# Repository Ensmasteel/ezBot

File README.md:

# EzBot Robotics Team Portfolio

Welcome to the EzBot Robotics Team portfolio website! This GitHub Pages site showcases our team's projects, achievements, and innovations in robotics.

## About This Site

This website is built using:
- HTML5
- CSS3
- JavaScript (ES6+)
- GitHub Pages for hosting

## Local Development

To run this site locally:

1. Clone the repository
2. Open `index.html` in your web browser
3. Or serve it using a local server:
   ```bash
   # Using Python 3
   python -m http.server 8000
   
   # Using Node.js (if you have live-server installed)
   npx live-server
   ```

## Deployment

This site is automatically deployed to GitHub Pages when changes are pushed to the main branch.

## Project Structure

```
├── index.html          # Main homepage
├── style.css          # Main stylesheet
├── script.js          # JavaScript functionality
├── README.md          # This file
└── assets/            # Images and other assets (to be added)
```

## Features

- Responsive design that works on all devices
- Smooth scrolling navigation
- Modern CSS with animations
- Clean, professional layout
- Optimized for GitHub Pages

## Customization

To customize this site for your robotics team:

1. Update the team name in `index.html`
2. Modify colors and styling in `style.css`
3. Add your team's projects and member information
4. Include your team's logo and images in an `assets/` folder

## Contributing

Team members can contribute by:
1. Forking the repository
2. Making changes
3. Submitting a pull request

## Contact

For questions about this website, please contact the EzBot team.

---

Built with ❤️ by the EzBot Robotics Team

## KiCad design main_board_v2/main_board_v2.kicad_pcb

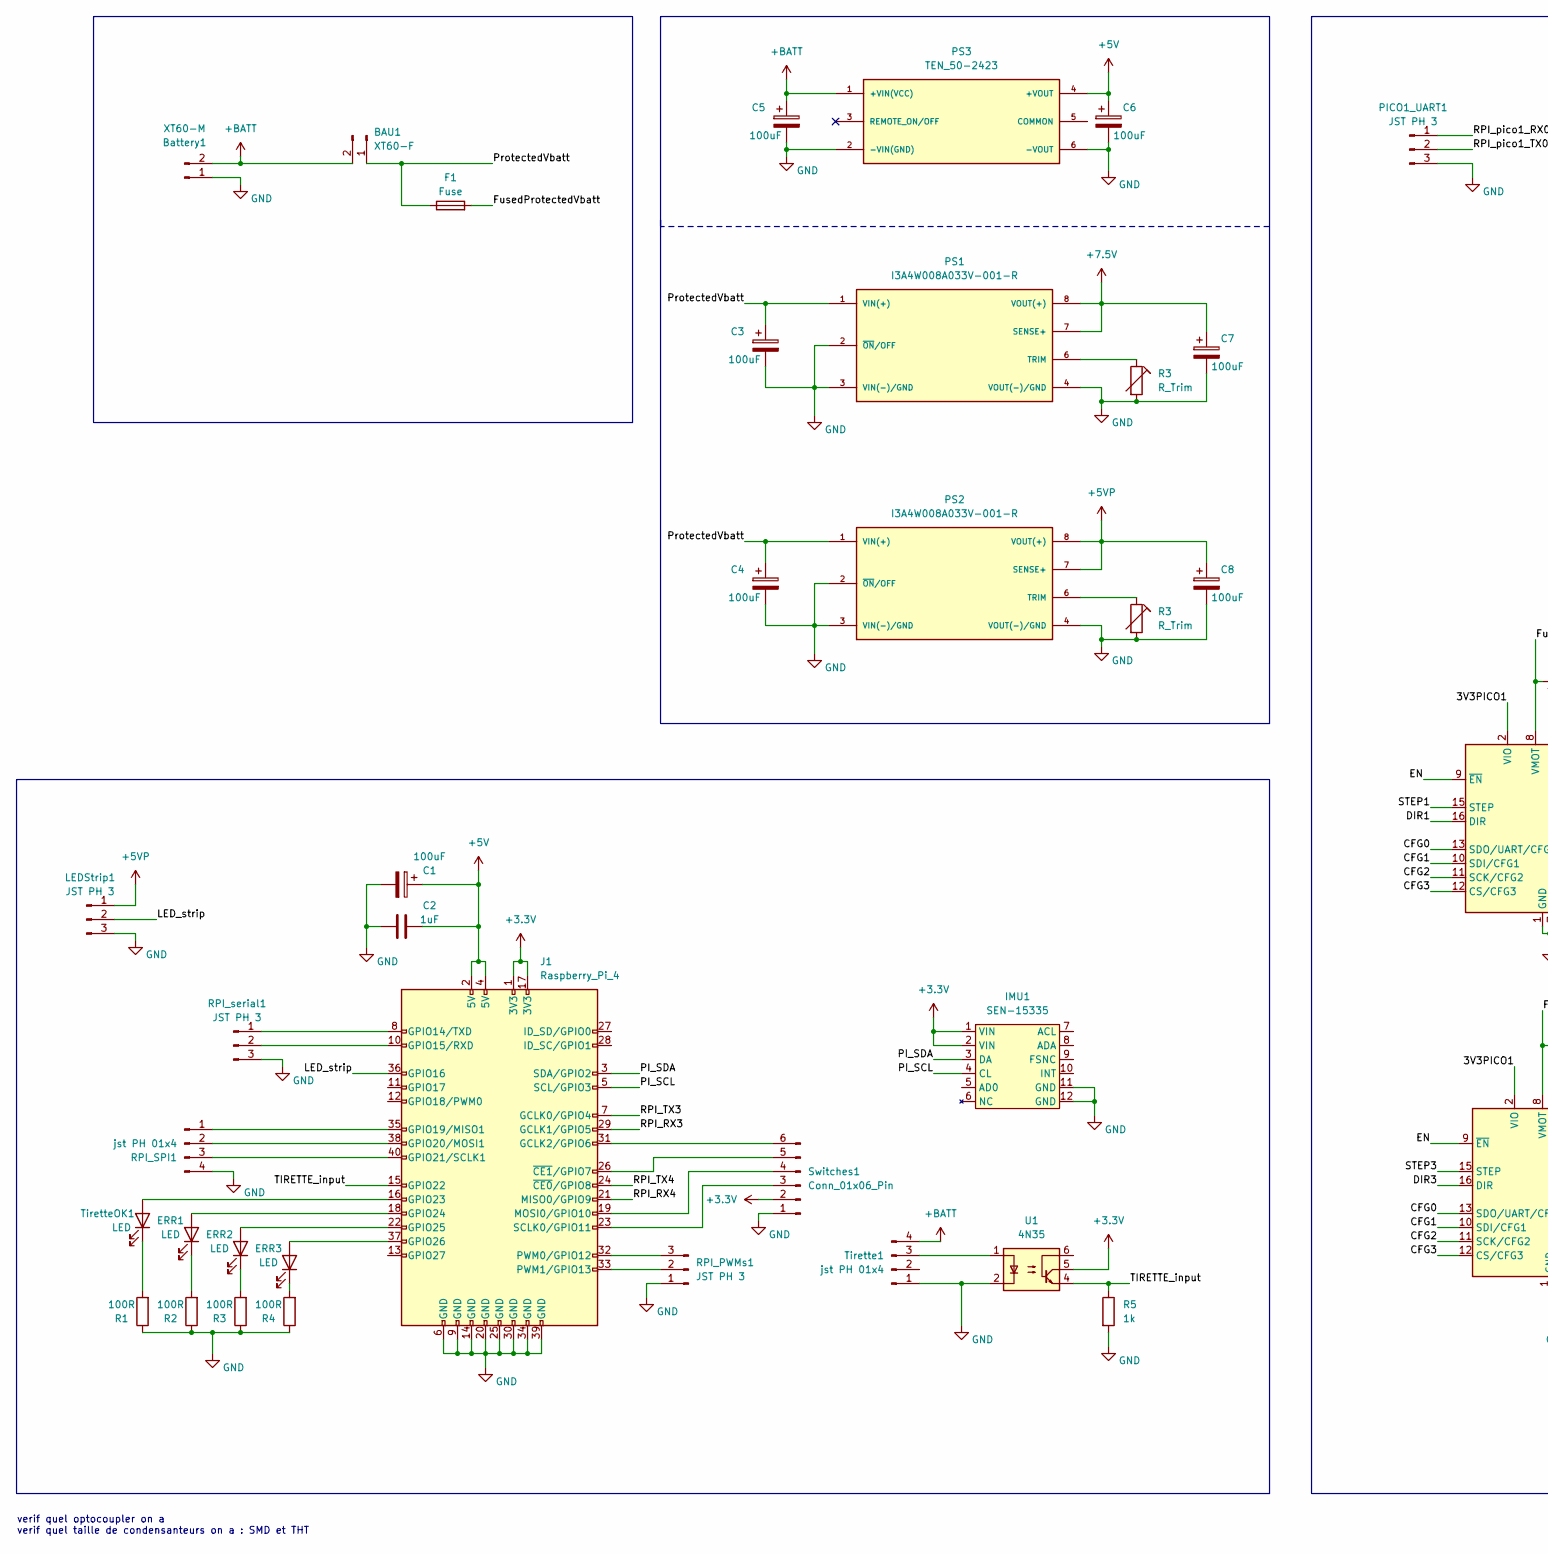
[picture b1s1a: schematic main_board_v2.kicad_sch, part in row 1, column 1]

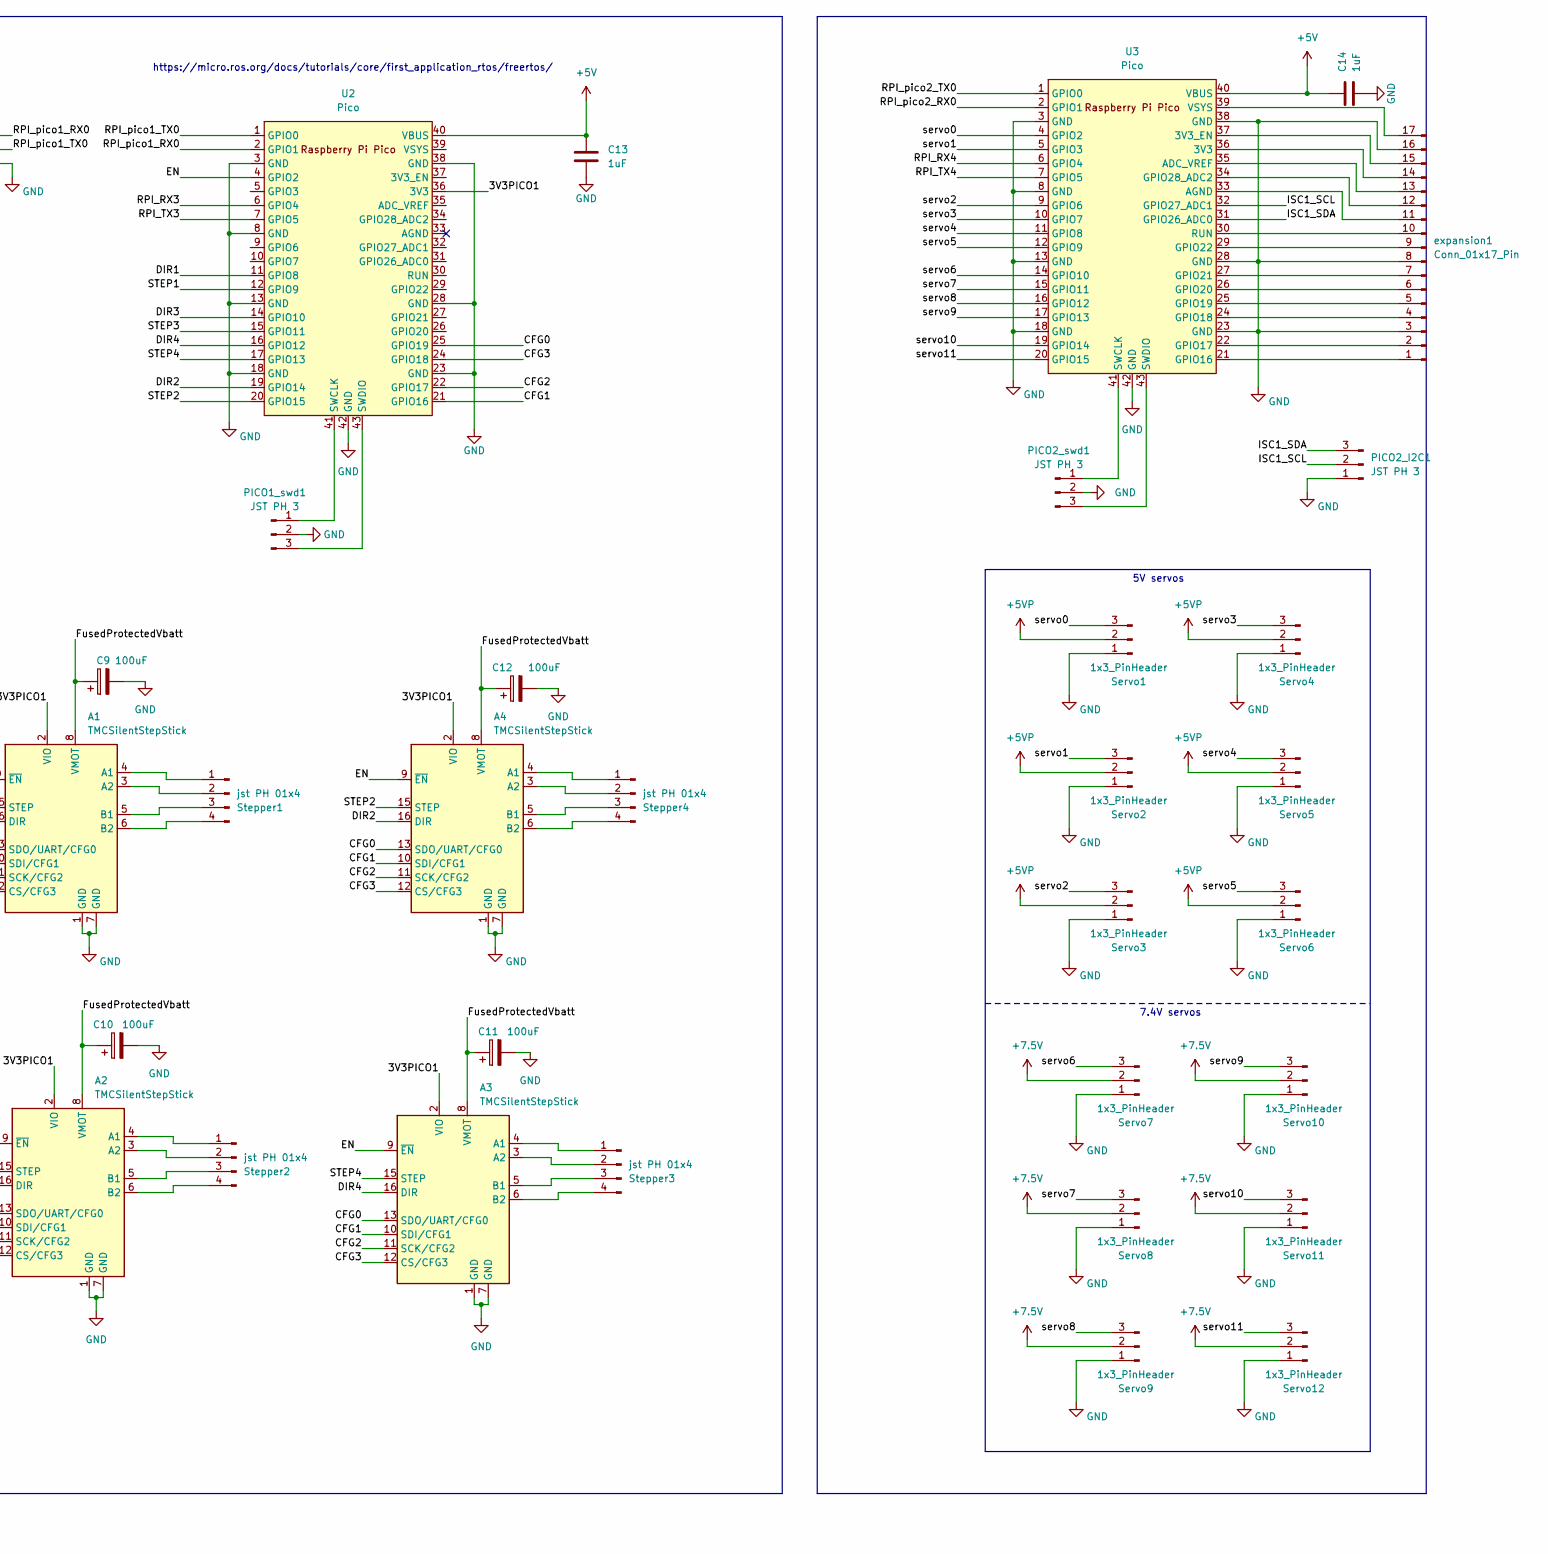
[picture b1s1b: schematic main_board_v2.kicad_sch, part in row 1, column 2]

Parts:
A1, A2, A3, A4: TMCSilentStepStick; TMCStick
BAU1: XT60-F; AMASS_XT60-F_1x02_P7.20mm_Vertical
Battery1: XT60-M; AMASS_XT60-M_1x02_P7.20mm_Vertical
C1, C3, C4, C5, C6, C7, C8, C9, C10, C11, C12: 100uF; C_Radial_D6.3mm_H11.0mm_P2.50mm
C2, C13, C14: 1uF; C_0805_2012Metric
ERR1, ERR2, ERR3: LED; LED_0805_2012Metric
F1: Fuse; Fuseholder_Blade_ATO_Littelfuse_Pudenz_2_Pin
IMU1: SEN-15335
J1: Raspberry_Pi_4
LEDStrip1: JST PH 3; JST_PH_B3B-PH-K_1x03_P2.00mm_Vertical
PICO1_UART1, PICO1_swd1, PICO2_I2C1, PICO2_swd1: JST PH 3; JST_PH_B3B-PH-K_1x03_P2.00mm_Vertical
PS1, PS2: I3A4W008A033V-001-R; CONV_I3A4W008A033V-001-R
PS3: TEN_50-2423; CONV_TEN_30-2423
R1, R2, R3, R4: 100R; R_1206_3216Metric
R5: 1k; R_1206_3216Metric
RPI_PWMs1: JST PH 3; JST_PH_B3B-PH-K_1x03_P2.00mm_Vertical
RPI_SPI1: jst PH 01x4; JST_PH_B4B-PH-K_1x04_P2.00mm_Vertical
RPI_serial1: JST PH 3; JST_PH_B3B-PH-K_1x03_P2.00mm_Vertical
Servo1, Servo2, Servo3, Servo4, Servo5, Servo6, Servo7, Servo8, Servo9, Servo10, Servo11, Servo12: 1x3_PinHeader; PinHeader_1x03_P2.54mm_Vertical
Stepper1, Stepper2, Stepper3, Stepper4: jst PH 01x4; JST_PH_B4B-PH-K_1x04_P2.00mm_Vertical
Switches1: Conn_01x06_Pin; JST_PH_B6B-PH-K_1x06_P2.00mm_Vertical
Tirette1: jst PH 01x4; JST_PH_B4B-PH-K_1x04_P2.00mm_Vertical
TiretteOK1: LED; LED_0805_2012Metric
U1: 4N35; DIP-6_W7.62mm
U2, U3: Pico; RPi_Pico_SMD_TH
expansion1: Conn_01x17_Pin; PinHeader_1x17_P2.54mm_Vertical

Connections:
+3.3V: IMU1.1 (VIN), IMU1.2 (VIN), J1.1 (3V3), J1.17 (3V3), Switches1.2, U1.5
+5V: C1.1, C2.2, C6.1, C13.1, C14.1, J1.2 (5V), J1.4 (5V), PS3.4 (+VOUT), U2.40 (VBUS), U3.40 (VBUS)
+5VP: C8.1, LEDStrip1.1, PS2.7 (SENSE+), PS2.8 (VOUT(+)), Servo1.2, Servo2.2, Servo3.2, Servo4.2, Servo5.2, Servo6.2
+7.5V: C7.1, PS1.7 (SENSE+), PS1.8 (VOUT(+)), Servo7.2, Servo8.2, Servo9.2, Servo10.2, Servo11.2, Servo12.2
+BATT: BAU1.2, Battery1.2, C5.1, PS3.1 (+VIN(VCC)), Tirette1.4
/3V3PICO1: A1.2 (VIO), A2.2 (VIO), A3.2 (VIO), A4.2 (VIO), U2.36 (3V3)
/CFG0: A1.13 (SDO/UART/CFG0), A2.13 (SDO/UART/CFG0), A3.13 (SDO/UART/CFG0), A4.13 (SDO/UART/CFG0), U2.25 (GPIO19)
/CFG1: A1.10 (SDI/CFG1), A2.10 (SDI/CFG1), A3.10 (SDI/CFG1), A4.10 (SDI/CFG1), U2.21 (GPIO16)
/CFG2: A1.11 (SCK/CFG2), A2.11 (SCK/CFG2), A3.11 (SCK/CFG2), A4.11 (SCK/CFG2), U2.22 (GPIO17)
/CFG3: A1.12 (CS/CFG3), A2.12 (CS/CFG3), A3.12 (CS/CFG3), A4.12 (CS/CFG3), U2.24 (GPIO18)
/DIR1: A1.16 (DIR), U2.11 (GPIO8)
/DIR2: A4.16 (DIR), U2.19 (GPIO14)
/DIR3: A2.16 (DIR), U2.14 (GPIO10)
/DIR4: A3.16 (DIR), U2.16 (GPIO12)
/EN: A1.9 (~EN), A2.9 (~EN), A3.9 (~EN), A4.9 (~EN), U2.4 (GPIO2)
/FusedProtectedVbatt: A1.8 (VMOT), A2.8 (VMOT), A3.8 (VMOT), A4.8 (VMOT), C9.1, C10.1, C11.1, C12.1, F1.2
/ISC1_SCL: PICO2_I2C1.2, U3.32 (GPIO27_ADC1)
/ISC1_SDA: PICO2_I2C1.3, U3.31 (GPIO26_ADC0)
/LED_strip: J1.36 (GPIO16), LEDStrip1.2
/PI_SCL: IMU1.4 (CL), J1.5 (SCL/GPIO3)
/PI_SDA: IMU1.3 (DA), J1.3 (SDA/GPIO2)
/ProtectedVbatt: BAU1.1, C3.1, C4.1, F1.1, PS1.1 (VIN(+)), PS2.1 (VIN(+))
/RPI_RX3: J1.29 (GCLK1/GPIO5), U2.6 (GPIO4)
/RPI_RX4: J1.21 (MISO0/GPIO9), U3.6 (GPIO4)
/RPI_TX3: J1.7 (GCLK0/GPIO4), U2.7 (GPIO5)
/RPI_TX4: J1.24 (~CE0/GPIO8), U3.7 (GPIO5)
/RPI_pico1_RX0: PICO1_UART1.1, U2.2 (GPIO1)
/RPI_pico1_TX0: PICO1_UART1.2, U2.1 (GPIO0)
/RPI_pico2_RX0: U3.2 (GPIO1)
/RPI_pico2_TX0: U3.1 (GPIO0)
/STEP1: A1.15 (STEP), U2.12 (GPIO9)
/STEP2: A4.15 (STEP), U2.20 (GPIO15)
/STEP3: A2.15 (STEP), U2.15 (GPIO11)
/STEP4: A3.15 (STEP), U2.17 (GPIO13)
/TIRETTE_input: J1.15 (GPIO22), R5.1, U1.4
/servo0: Servo1.3, U3.4 (GPIO2)
/servo1: Servo2.3, U3.5 (GPIO3)
/servo2: Servo3.3, U3.9 (GPIO6)
/servo3: Servo4.3, U3.10 (GPIO7)
/servo4: Servo5.3, U3.11 (GPIO8)
/servo5: Servo6.3, U3.12 (GPIO9)
/servo6: Servo7.3, U3.14 (GPIO10)
/servo7: Servo8.3, U3.15 (GPIO11)
/servo8: Servo9.3, U3.16 (GPIO12)
/servo9: Servo10.3, U3.17 (GPIO13)
/servo10: Servo11.3, U3.19 (GPIO14)
/servo11: Servo12.3, U3.20 (GPIO15)
unnamed: A1.4 (A1), Stepper1.1
unnamed: A1.3 (A2), Stepper1.2
unnamed: A1.5 (B1), Stepper1.3
unnamed: A1.6 (B2), Stepper1.4
unnamed: A2.4 (A1), Stepper2.1
unnamed: A2.3 (A2), Stepper2.2
unnamed: A2.5 (B1), Stepper2.3
unnamed: A2.6 (B2), Stepper2.4
unnamed: A3.4 (A1), Stepper3.1
unnamed: A3.3 (A2), Stepper3.2
unnamed: A3.5 (B1), Stepper3.3
unnamed: A3.6 (B2), Stepper3.4
unnamed: A4.4 (A1), Stepper4.1
unnamed: A4.3 (A2), Stepper4.2
unnamed: A4.5 (B1), Stepper4.3
unnamed: A4.6 (B2), Stepper4.4
unnamed: ERR1.2 (A), J1.18 (GPIO24)
unnamed: ERR1.1 (K), R2.2
unnamed: ERR2.2 (A), J1.22 (GPIO25)
unnamed: ERR3.2 (A), J1.37 (GPIO26)
unnamed: ERR3.1 (K), R4.2
unnamed: J1.31 (GCLK2/GPIO6), Switches1.6
unnamed: J1.8 (GPIO14/TXD), RPI_serial1.1
unnamed: J1.10 (GPIO15/RXD), RPI_serial1.2
unnamed: J1.35 (GPIO19/MISO1), RPI_SPI1.1
unnamed: J1.38 (GPIO20/MOSI1), RPI_SPI1.2
unnamed: J1.40 (GPIO21/SCLK1), RPI_SPI1.3
unnamed: J1.16 (GPIO23), TiretteOK1.2 (A)
unnamed: J1.19 (MOSI0/GPIO10), Switches1.4
unnamed: J1.32 (PWM0/GPIO12), RPI_PWMs1.3
unnamed: J1.33 (PWM1/GPIO13), RPI_PWMs1.2
unnamed: J1.23 (SCLK0/GPIO11), Switches1.3
unnamed: J1.26 (~CE1/GPIO7), Switches1.5
unnamed: PICO1_swd1.1, U2.41 (SWCLK)
unnamed: PICO1_swd1.3, U2.43 (SWDIO)
unnamed: PICO2_swd1.1, U3.41 (SWCLK)
unnamed: PICO2_swd1.3, U3.43 (SWDIO)
unnamed: Tirette1.3, U1.1
unnamed: R1.2, TiretteOK1.1 (K)
unnamed: U3.36 (3V3), expansion1.14
unnamed: U3.37 (3V3_EN), expansion1.15
unnamed: U3.35 (ADC_VREF), expansion1.13
unnamed: U3.33 (AGND), expansion1.11
unnamed: U3.21 (GPIO16), expansion1.1
unnamed: U3.22 (GPIO17), expansion1.2
unnamed: U3.24 (GPIO18), expansion1.4
unnamed: U3.25 (GPIO19), expansion1.5
unnamed: U3.26 (GPIO20), expansion1.6
unnamed: U3.27 (GPIO21), expansion1.7
unnamed: U3.29 (GPIO22), expansion1.9
unnamed: U3.34 (GPIO28_ADC2), expansion1.12
unnamed: U3.30 (RUN), expansion1.10
unnamed: U3.39 (VSYS), expansion1.17

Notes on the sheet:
5V servos
verif quel optocoupler on a verif quel taille de condensanteurs on a : SMD et THT
https://micro.ros.org/docs/tutorials/core/first_application_rtos/freertos/
7.4V servos

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
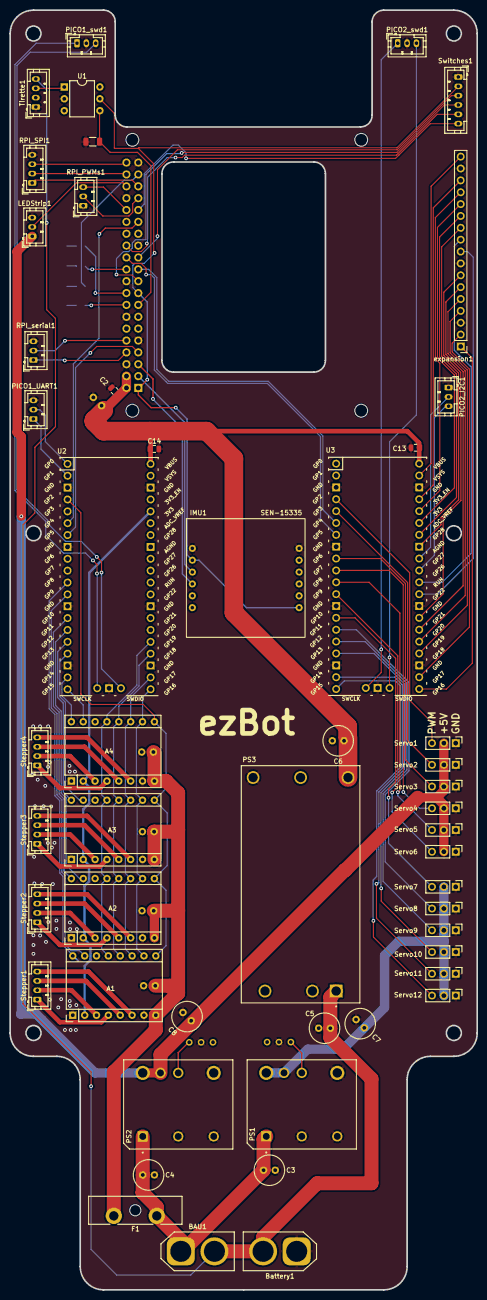
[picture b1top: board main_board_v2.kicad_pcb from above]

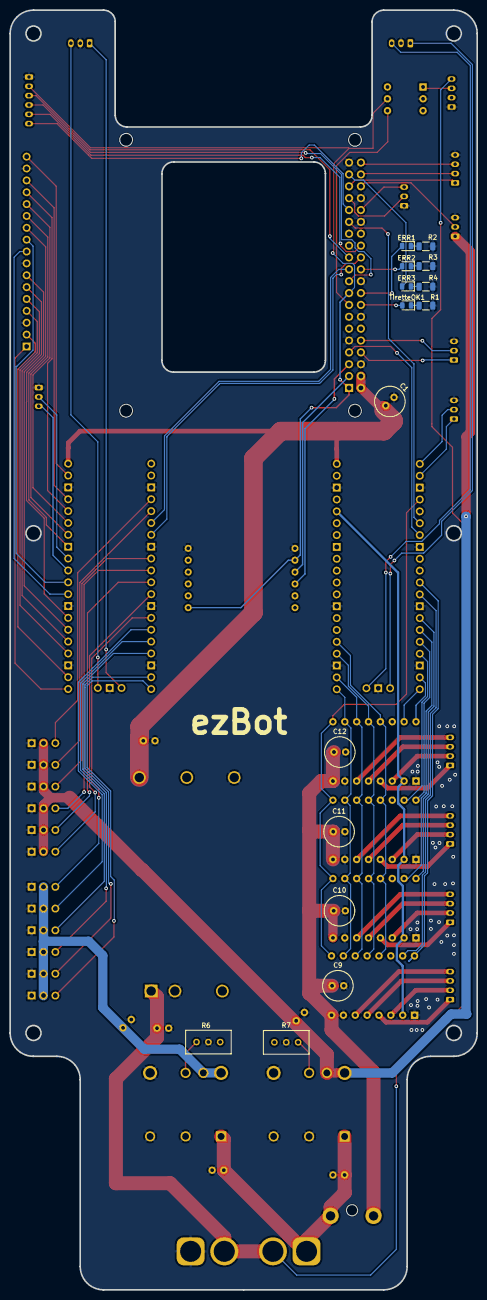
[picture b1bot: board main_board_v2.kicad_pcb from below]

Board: 2 copper layers, 100.0 x 274.0 mm, 67 parts (15 on the bottom side), 102 nets.

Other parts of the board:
R6, R7: R_Trim; Potentiometer_Bourns_3296W_Vertical

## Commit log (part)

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2023-08-03 Creation of new orphan branch "electronic"
2023-08-04 Test
2023-08-04 Added Humble Hawksbill Image for readme
2023-08-04 Modified README.md
2023-08-04 Created ROS2 workspace with colcon
2023-08-05 Added main files
    Currently only one main-skeleton, but sub skeletons can be used for sub assemblies
2023-08-05 Added Fasteners and others
2023-08-06 Amost Finished Holonimc wheel
    Missing holes and (3D printed) Hub
2023-08-06 These nuts are M3
2023-08-08 Added Nema17 motor
2023-08-08 Almost finished holonomic wheel
2023-09-11 Added rules and rules images
    Images could be used in some readmes
2023-09-11 Added table to main readme
2023-09-11 changed path README.md
2023-09-12 Added png version of main vinyl
2023-09-12 Added stl of corrected fixed table
2023-09-12 Added texture file and textured the table in Blender
2023-10-17 Nema23
2023-10-17 Created project
2023-10-17 No, this is the project's creation
2023-10-23 Created MotorAndWheelAssembly and added many things to skeleton
2023-10-25 Center base and center chassis creation
2023-10-26 Added the four rails
2023-10-26 Changed the propulsion block chassis
    now kind of works
    still needs mounting holes
2023-10-28 Added bolts to propulsion module and parameter for width
2023-10-28 Changed some constraints
2023-10-28 Before scenes schenanigans
2023-10-28 Tested parameter unitsize -> works kinda
2023-10-30 Reduced joint thickness so that NEMA17 motor can be inserted
2023-11-01 Passage cables moteurs chassis centre et chassis propulsion
2023-11-01 inserts in center chassis
2023-11-01 Added chanfers
2023-11-01 Started top
2023-11-02 Ajout de vis pour rail NE
2023-11-02 Holes ans screws
2023-11-02 All rails have now bottom holes
2023-11-03 Added PCB placeholder
2023-11-03 Modified TopCenterChassis
2023-11-03 Hid TopSkeleton
2023-11-03 Added Holes to Rails
2023-11-03 Mine is better
2023-11-04 Added some homemade footprints
    TMCSilentStepStick and IMU
2023-11-04 Added battery placeholder
2023-11-04 Used parameter for M3 holes on TopCenterChassis
2023-11-04 Battery Work
2023-11-04 Added battery prototype to main product
2023-11-05 Added traco and tdk regulators, and IMU and more
2023-11-05 Added headers and corrected 3d model of pico
2023-11-13 Work, lots of
2023-11-23 Work it seams
2023-11-23 Added plug for raspberry switches and corrected all DRCs
2023-11-24 Created part from product to export to gazebo
2023-11-24 Added .dae file of the table with UV map
2023-11-24 removed unnecessaty built files and added ezbot_gazebo pkg
2023-11-29 Added ldrobot lidar and some launch files
2023-11-29 Removed empty folder
2023-11-29 Added .gitignore file with the log, build, and install folders
2023-12-01 Lidar transition launch file now works
2023-12-01 Added testing folder for RP pico (propulsion)
2023-12-18 Robot description and simulation
2023-12-18 Rm folder
2023-12-18 Added robot description, launch file for simul (based on Mathys myBot)
2023-12-18 updated scale
2023-12-18 Added verbose launch of simulation
2023-12-18 Changed color of one of the wheels
2023-12-18 Added workflow in ezBot branch
2023-12-18 removed tabs
2023-12-19 Attempt to fix copyright issue
2023-12-19 removed empty file
2023-12-22 joystick and launch file
2023-12-22 robot description changes
2023-12-22 Delete .vscode directory
    do not push .vscode directory
2023-12-22 Added omnidirectional controller from axebot
2024-01-10 Changed dimensions of lidar and camera resolution.
2024-01-11 Added world folder to the install path the launch file for the simulation can now be launched from anywhere
2024-01-12 Changed lidar frame name
2024-01-12 Fixed the bug where we could only launch from src
    We could only launch launch_sim.launch.py from /src directory as the path were relative
2024-01-12 added an aruco marker on top of the robot
2024-01-12 work
2024-01-17 tag aruco on the robot
2024-01-17 Changed mu1
2024-01-17 Added min_depth tag to (almost) eliminate the robot from drifting
2024-01-17 Added real robot launch file
2024-01-17 Added main rpi-pico project It is for now a platformio progect and based on articulated's robotic project
2024-01-17 Made a hardware interface based on diffdrive-arduino ! Not tested yet !
2024-01-19 Added homemade controller to not user ros2control
2024-01-24 Added docker files for arm, and scripts for build and run
2024-01-24 Homemade controller
    Now sends correctly to emulated serial, needs testing with real serial
2024-01-24 Controller configuration for ros2_control
    Not in use currentyl
2024-01-24 launch file for the real robot
2024-01-24 added marker detection for the second camera
2024-01-24 Updated RailDrillingTool and LidarBase
2024-01-24 Changed _ to .
2024-01-26 Changed from Opencv to opencv-python in dependencies
2024-01-26 changed again to python 3
2024-01-29 Added solar panel model
2024-01-29 Added solar panel to table
2024-01-29 changed image name and added display
2024-01-29 Added comment test
2024-01-29 removed temp package.xml
2024-01-29 Added it back
2024-01-29 WILL THE RUN WORK ??
2024-01-29 Changed gazebo omni drive kinematics now drive straight chen cmd_vel = x
2024-01-31 removed unused omnidirectional controller
2024-02-05 Changed from 21700 to 18650
    Still need to change names of parts and instances
2024-03-30 Changed robot height to actual height (343mm rails)
2024-03-30 Fixed the PCB's position
    the PCB'ss positition was deriver from the placeholder's position. Howerver, the PCB placeholder was not dimensioned correctly (dimmensioned using robot's contraints and not pure dimensions)
2024-03-31 Added holes to rails for PCB (only center for now)
2024-03-31 Added assembly of rail drilling tool and one rail and fixed tool
    The product is used to verify the alignment of the holes in the tool and in the rails (SW for now)
2024-03-31 Print file of the rail drilling tool
2024-04-04 I don't know why every file changed but made slots to the top center
2024-04-09 Rework on the battery and the top chassis
2024-04-09 Added Lidar spacer, and support
    also modified the existing "lidar base" part to fit the new battery
2024-04-10 Printed this version of the Lidar Base and Spacer
2024-04-17 Printed test receiver plate and added wheel hubs
2024-04-18 Added a way to fix the receiver plate
2024-04-21 Set logger to info in launch file if not set
2024-04-21 Be able to launch docker on raspberry's boot (not used)
2024-04-21 removed ldlidar submodule
2024-04-21 Renamed ezbot_gazebo to ezbot_simulation
2024-04-21 Moved launch_sim.launch.py to simulation folder
2024-04-21 rm unnecessary turtle launch file
2024-04-21 Renamed ezbot_descr_simul to ezbot_robot
    This is to make a clearer sepperation between simulation and real robot codebases
2024-04-21 Changed all instances of ezbot_descr_simul to ezbot_robot
2024-04-22 ros2_control seem to be working, testing the communication with Pico
2024-04-22 Changed serial port and how yaml file is configured
2024-04-23 Control module and other
2024-04-23 Removed TEMPORARELY THE RESPONSE PART
2024-04-23 Added logger to see what is sent
2024-04-23 testing old controller
2024-04-23 renamed launch file
2024-04-23 ttyAMA3->ttyAMA1
2024-04-23 ttyAMA3->ttyAMA1 in yaml file
2024-04-23 added logger to rppico_comms
2024-04-24 Changed Serial port and dimensions
2024-04-24 removed long timer, reverted to 1 sec
2024-04-24 Tried to add speed limit, first test without changing yaml file
2024-04-24 Oupsi, forgot to initialize previous_commands
2024-04-24 Fixed parameter naming scheme
2024-04-24 First test with velocity limit
2024-04-24 Didn't limit the correct speed I think
2024-04-24 Fixed parameter naming
2024-04-26 Cleanup old code and uncommented tf odom publishing
2024-04-26 added frame id to odometry message
2024-04-26 Changed wheel radius to half
2024-04-26 changed how open loop odom is calculated
2024-04-26 log test
2024-04-26 Added comment about current microsteping setting
2024-04-26 removed eronous divions by loop rate
2024-04-26 Scaled acceleration more appropriately
2024-04-28 Better but not perfect robot's radius
2024-04-29 Added imu and filter to launch file
2024-04-29 Added delay to filter
2024-04-29 missing s
2024-04-29 renamaed rpi-pico to rpi-pico-propulsion
2024-04-29 Duplicated rpipico for pico2 (acutators)
    One servo is at least working, should be able to handle more, needs testing
2024-04-29 New hardware interface for actuator pico interaction (servos)
2024-04-29 renamed second ros2_control hardware interface
2024-04-29 tried to fix allocation error
2024-04-29 changed position of return and logger
2024-04-29 Reverted the string handling
2024-04-29 added default no param constructor to Servo class
2024-04-29 Commented logger
2024-04-30 Added joint ldlidar_base
2024-04-30 changed description xacro
2024-04-30 rotated joint
2024-04-30 wrong way
2024-04-30 Added slam configuration file based on defualt file
2024-04-30 trying to fix wrong direction right left
2024-04-30 Changing signs until it works
2024-05-02 Should fix error when adding other servos
2024-05-02 Applied patches done on raspberryPi
2024-05-02 Missed parantheses
2024-05-02 oupsi, I removed the IMU by accident
2024-05-02 Changed how the launch file is called
2024-05-02 third time's the charm
2024-05-02 ahhhhhhhhhhhhhhhhhhhh
2024-05-02 Changed launch delays and how the robot description is passed
2024-05-02 Changed where the lidar publishes it's transform
2024-05-02 reverted previous changes on real_robot.lauch.py
2024-05-02 Changed rotation of lidar yet again
2024-05-02 Trying to isolate nav2 and the lidar : conflicting lifecycle managers
2024-05-02 Changed namespace to not the node name
2024-05-02 changed who is the parent and who is the child
2024-05-04 Update package.xml and removed libi2c dependency
2024-05-06 Added launch and params files from nav2 brningup and changed some topics
2024-05-06 Changed scanning resolution and topic it listens to
2024-05-06 removed unused .gitmodules file
2024-05-06 Changed from exec depend to depend
2024-05-06 Changed which Github action to use
2024-05-06 Changed actions version
2024-05-06 Disabled version checking in LIDAR code
2024-05-06 Disabled lidar_node as well
2024-05-08 Added first tirette node test
2024-05-08 added debug messages
2024-05-08 removed unnecessary code
2024-05-08 checking what value gpiod_line_request_input_flags returns
2024-05-08 Added debug messsages
2024-05-08 changed pin to actual tirette pin
2024-05-08 Code needed for homologation
2024-05-09 Added match launch file with all required nodes and robtot itself
2024-05-09 changed setup of match1 node
2024-05-09 changed speed and time calculation
2024-05-09 Switched footprint to be parent
2024-05-09 trying to englobe everytinh under the /lidar namespace
2024-05-09 time used for 1st match
2024-05-09 Revert "Switched footprint to be parent"
    This reverts commit dbf26b40ae5b945b81821831a86dcced3bf0e6af.
2024-05-09 Added link to ldlidar_link in lidar.xacro
2024-05-09 Removed namespace and set it via name
2024-05-09 Fix a mess I made but didn't notice
2024-05-09 renamed everything to the /lidar namespace
2024-05-10 Changed how we detect enemy (IR interference)
2024-05-11 Changed check lidar
2024-05-15 Nav2 kind of works with slam IRL
2024-05-16 Nav2 now goes correctly to goal (at least in simulation)
2025-01-29 Moved packages to src directory and fix dependencies
2025-01-29 Change workflow runner type
    ubuntu-latest is now 24.04, nut we want 22.04 for ROS2 Humble
2025-01-29 Did they change the name of their action ?
2025-01-29 Added param to build without docker cache
2025-01-29 Update action version
2025-01-29 revert to version with sudo
2025-01-29 Added gpiod as dependencies
2025-01-29 Added gpiod as an install in GH action
2025-01-29 added udev as a GH action dependency
2025-01-29 make the gpiod the lib and not just gpiod
2025-06-07 All code that is on the robot after the robtics cup
2025-07-26 new gh pages branch
